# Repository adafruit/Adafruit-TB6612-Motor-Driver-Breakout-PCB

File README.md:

## Adafruit TB6612 Motor Driver Breakout PCB

<a href="http://www.adafruit.com/products/2448"><br/>
Click here to purchase one from the Adafruit shop</a>

PCB files for the Adafruit TB6612 Motor Driver Breakout. Format is EagleCAD schematic and board layout
* https://www.adafruit.com/product/2448

### DESCRIPTION
Spin two DC motors, step one bi-polar or uni-polar stepper, or fire off two solenoids with 1.2A per channel using the TB6612. These are perhaps better known as "the drivers in our assembled Adafruit Motorshield or Motor HAT." We really like these dual H-bridges, so if you want to control motors without a shield or HAT these are easy to include on any solderless breadboard or perma-proto.

We solder on TB6612 onto a breakout board for you here, with a polarity protection FET on the motor voltage input and a pullup on the "standby" enable pin. Each breakout chip contains two full H-bridges (four half H-bridges). That means you can drive 2-4 solenoids (only two can be active at a time, on opposite bridges), two DC motors bi-directionally, or one stepper motor. Just make sure they're good for 1.2 Amp or less of current, since that's the limit of this chip. They do handle a peak of 3A but that's just for a short amount of time, like 20 milliseconds. What we like most about this particular driver is that it comes with built in kick-back diodes internally so you don't have to worry about the inductive kick damaging your project or driver!

There's two digital inputs per H-bridge (one for each half of the bridge) as well as a PWM input per driver so you can control motor speed. Runs at 2.7V-5V logic. The motor voltage is separate from the logic voltage. Good for motor voltages from 4.5V up to 13.5V! This wont work well for 3V motors.

### License

Adafruit invests time and resources providing this open source design, please support Adafruit and open-source hardware by purchasing products from [Adafruit.com](https://www.adafruit.com)!

Creative Commons Attribution, Share-Alike license, check license.txt for more information All text above must be included in any redistribution - 
See license.txt for more information.

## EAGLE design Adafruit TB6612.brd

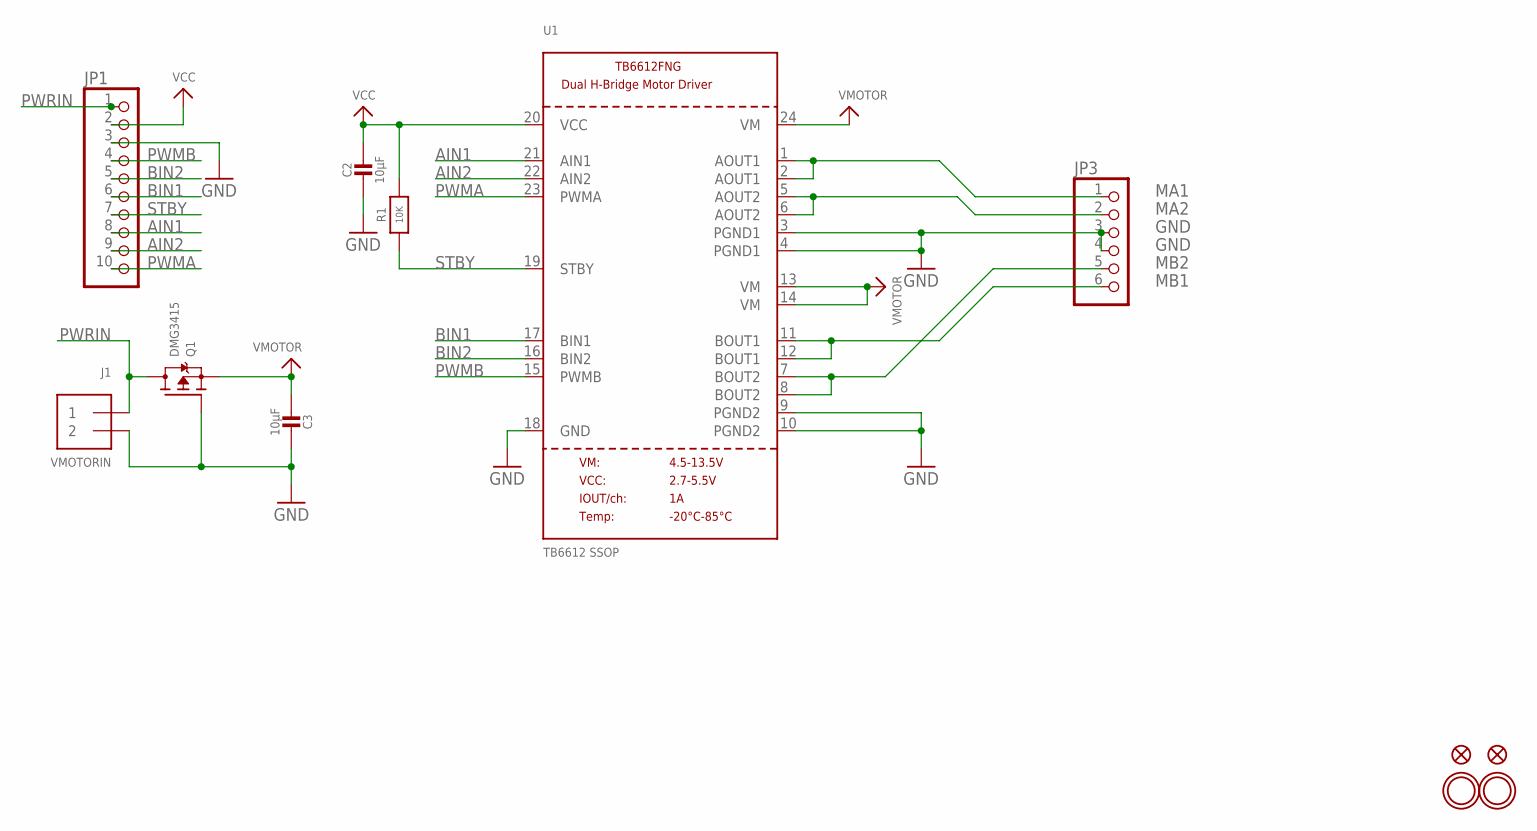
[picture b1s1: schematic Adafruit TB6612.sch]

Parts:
C2, C3: 10µF; 0805-NO
FID1, FID2: FIDUCIAL""; FIDUCIAL_1MM
J1: VMOTORIN; TERMBLOCK_1X2-3.5MM
JP1: HEADER-1X10THICKER; 1X10_ROUND_76
JP3: PINHD-1X6CB; 1X06-CLEANBIG
Q1: DMG3415; SOT23-WIDE
R1: 10K; 0805-NO
U1: TB6612 SSOP; SSOP24
U$13, U$14: MOUNTINGHOLE2.5; MOUNTINGHOLE_2.5_PLATED

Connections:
AIN1: JP1.8, U1.21 (AIN1)
AIN2: JP1.9, U1.22 (AIN2)
BIN1: JP1.6, U1.17 (BIN1)
BIN2: JP1.5, U1.16 (BIN2)
GND: C2.2, C3.2, J1.2, JP1.3, JP3.3, JP3.4, Q1.1 (G), U1.3 (PGND1), U1.4 (PGND1), U1.9 (PGND2), U1.10 (PGND2), U1.18 (GND)
MA1: JP3.1, U1.1 (AOUT1), U1.2 (AOUT1)
MA2: JP3.2, U1.5 (AOUT2), U1.6 (AOUT2)
MB1: JP3.6, U1.11 (BOUT1), U1.12 (BOUT1)
MB2: JP3.5, U1.7 (BOUT2), U1.8 (BOUT2)
PWMA: JP1.10, U1.23 (PWMA)
PWMB: JP1.4, U1.15 (PWMB)
PWRIN: J1.1, JP1.1, Q1.3 (D)
STBY: JP1.7, R1.1, U1.19 (STBY)
VCC: C2.1, JP1.2, R1.2, U1.20 (VCC)
VMOTOR: C3.1, Q1.2 (S), U1.13 (VM), U1.14 (VM), U1.24 (VM)

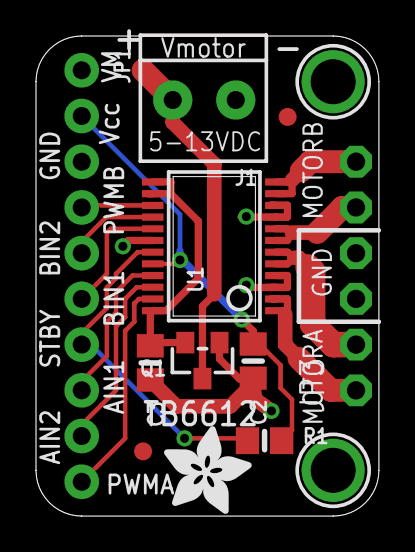
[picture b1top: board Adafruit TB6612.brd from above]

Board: 2 copper layers, 19.1 x 26.7 mm, 14 parts (1 on the bottom side), 15 nets.

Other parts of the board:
U$11: ADAFRUIT_3.5MM
U$15: ADAFRUIT_5MM

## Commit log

2016-10-01 init
